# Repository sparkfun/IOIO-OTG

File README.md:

IOIO-OTG
========

[*IOIO-OTG (DEV-11343)*](https://www.sparkfun.com/products/11343)

The IOIO-OTG is a development board specifically designed for advanced hardware I/O capapbilities to your Android or PC application.
This board also allows the user to leverage USB On-The-Go specification to connect as a host or as an accessory. 

Repository Contents
-------------------
* **/Hardware** - All Eagle design files (.brd, .sch, .STL)
* **/Production** - Test bed files and production panel files

Documentation
--------------

* **[Hookup Guide](https://learn.sparkfun.com/tutorials/ioio-otg-hookup-guide)** - Basic hookup guide for the IOIO-OTG.
* **[SparkFun Fritzing repo](https://github.com/sparkfun/Fritzing_Parts)** - Fritzing diagrams for SparkFun products.
* **[SparkFun 3D Model repo](https://github.com/sparkfun/3D_Models)** - 3D models of SparkFun products. 
* **[SparkFun Graphical Datasheets](https://github.com/sparkfun/Graphical_Datasheets)** -Graphical Datasheets for various SparkFun products.

Product Versions
----------------
* [v22b](https://www.sparkfun.com/products/13613)- Version 2.2b. Currently for sale.
* [v21] (https://www.sparkfun.com/products/retired/12633)- Version 2.1. Retired.

Version History
---------------
* [v2.2b](https://github.com/sparkfun/IOIO-OTG/tree/V_2.2b) - GitHub files v2.2b
* [v2.1](https://github.com/sparkfun/IOIO-OTG/tree/V_2.1) - GitHub files v2.1

License Information
-------------------
This product is _**open source**_! 

Please review the LICENSE.md file for license information. 

If you have any questions or concerns on licensing, please contact techsupport@sparkfun.com.

Distributed as-is; no warranty is given.

- Your friends at SparkFun.

The IOIO is a collaboration with Ytai Ben-Tsvi. You can find his repo [here](https://github.com/ytai/ioio/wiki).

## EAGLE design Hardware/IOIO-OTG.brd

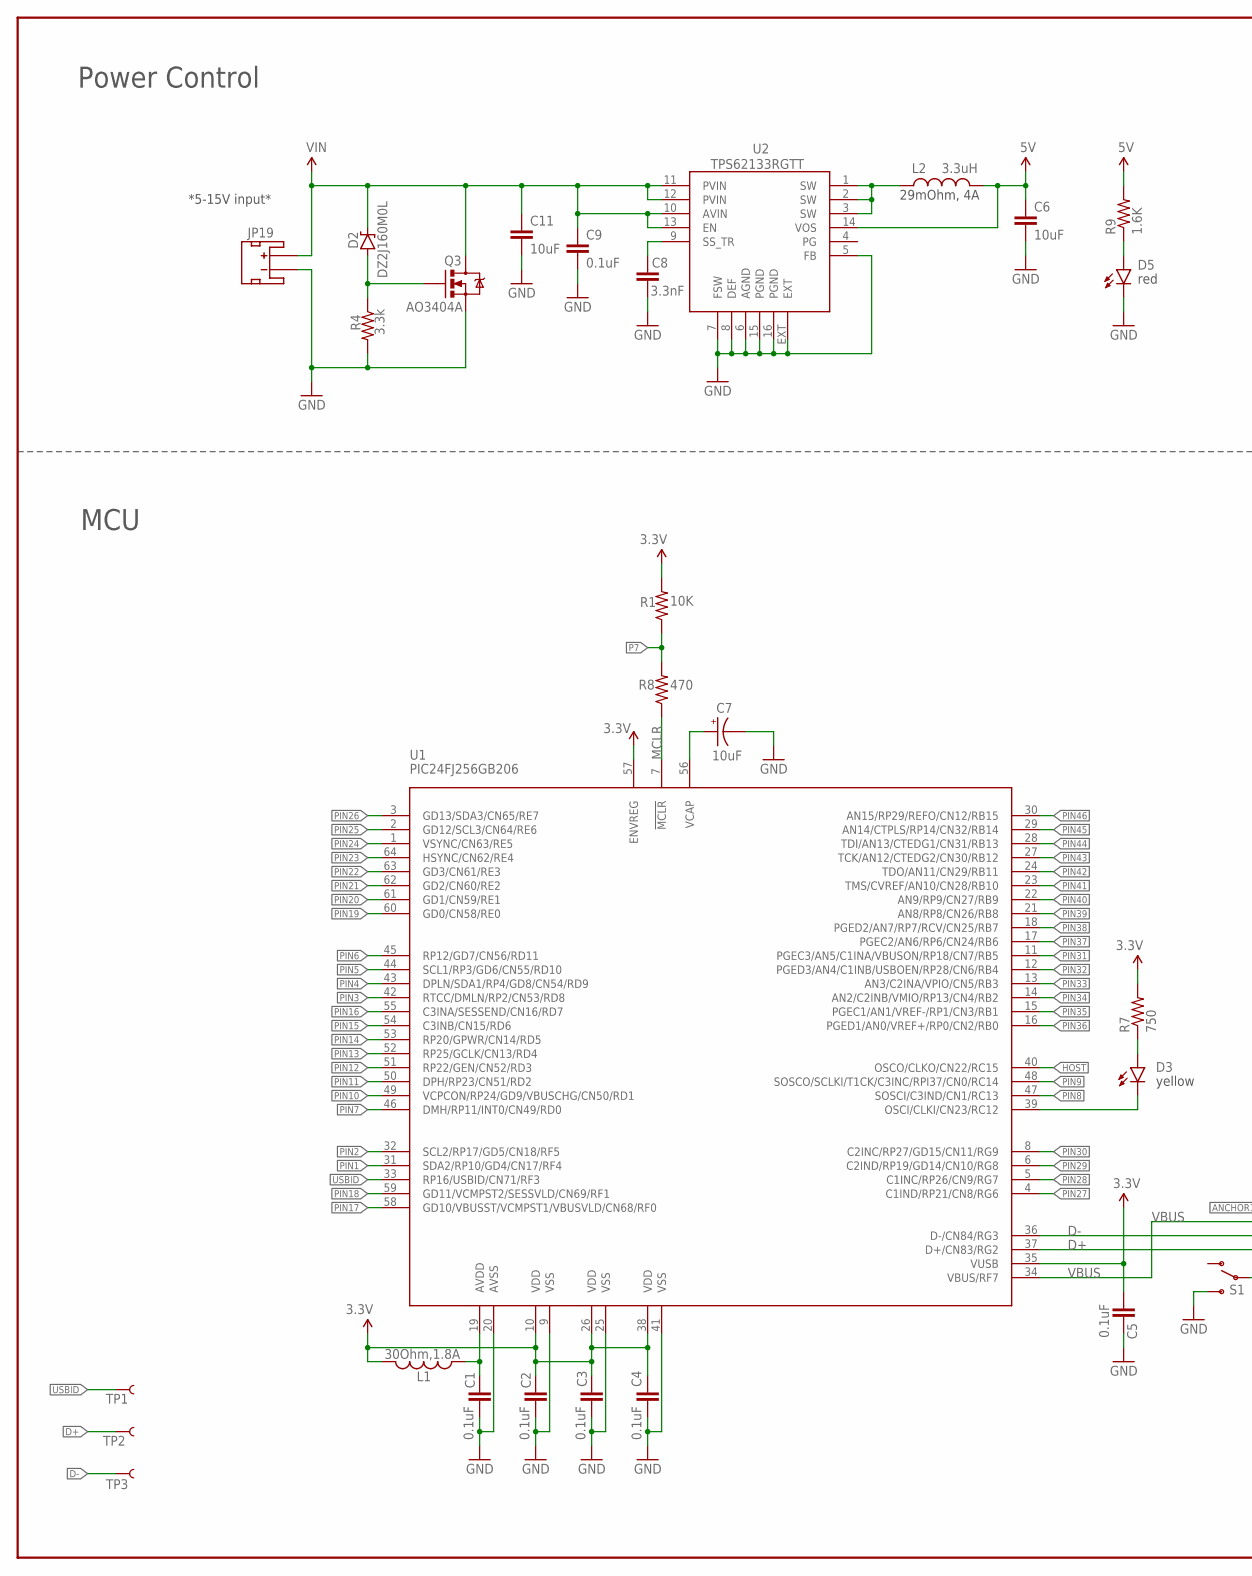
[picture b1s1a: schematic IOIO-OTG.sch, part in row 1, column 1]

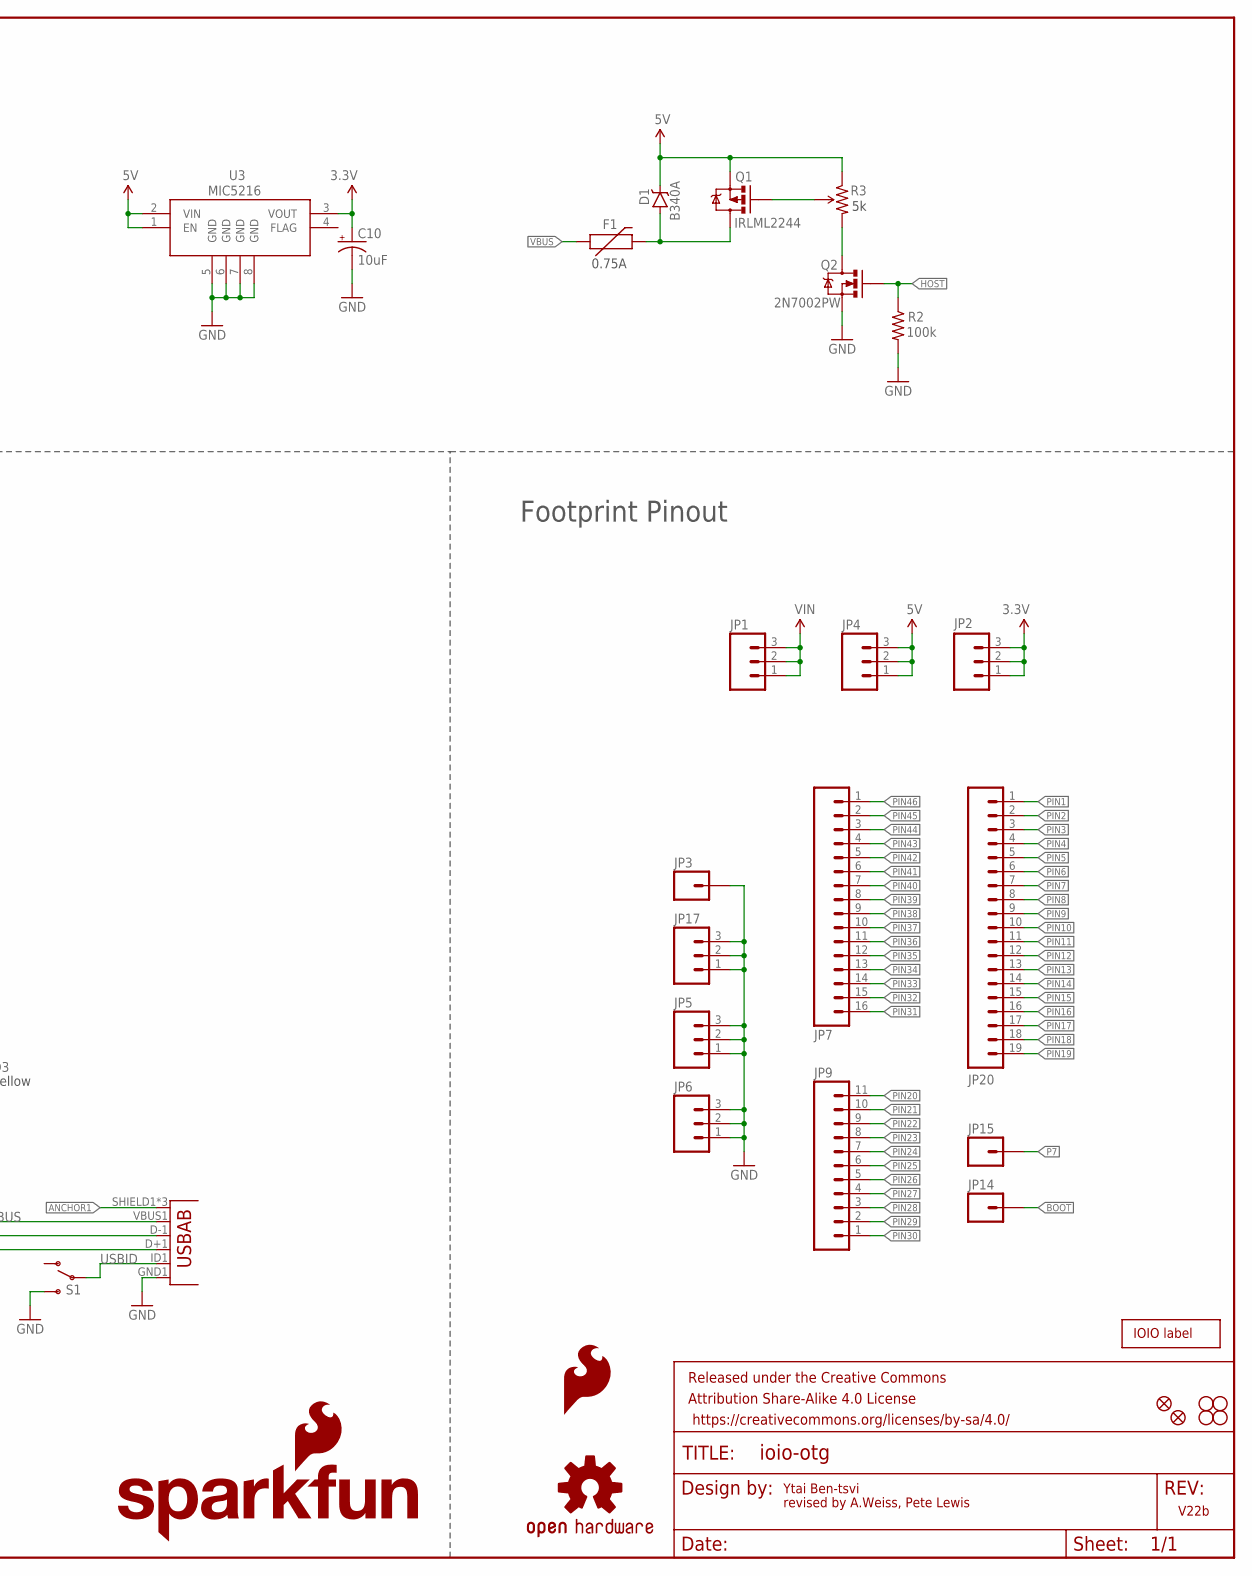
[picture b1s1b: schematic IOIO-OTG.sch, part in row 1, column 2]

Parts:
C1, C2, C3, C4, C5, C9: 0.1uF; 0603-CAP
C6: 10uF; 0805-CAP; PART# LMK212BJ106KG-T
C7: 10uF; EIA3216
C8: 3.3nF; 0603-CAP
C10: 10uF; EIA3216; PART# TAJA106K016RNJ
C11: 10uF; 1210; PART# UMK325C7106MM-T
D1: B340A; SMA-DIODE; PART# B340A
D2: DZ2J160M0L; PANASONIC_SMINI2-F5-B; PART# DZ2J150M0L
D3: Yellow; LED-0603
D5: Red; LED-0603
F1: 0.75A; PTC-1206; PART# 0ZCA0075FF2G
FRAME2: FRAME-LEDGER; CREATIVE_COMMONS
JP1, JP2, JP4, JP5, JP6, JP17: M03PTH; 1X03
JP3, JP14, JP15: M01PTH; 1X01
JP7: M161X16_NO_SILK; 1X16_NO_SILK
JP8, JP16: FIDUCIALUFIDUCIAL; MICRO-FIDUCIAL
JP9: M111X11_NO_SILK; 1X11_NO_SILK
JP10, JP11, JP12, JP13: STAND-OFF
JP19: JST; JST-2-SMD
JP20: M191X19_NO_SILK; 1X19_NO_SILK
JP21: AB MICRO USB; USB-AB-MICRO-SMD_V03
L1: 30Ohm,1.8A; 0603
L2: VLC5045T-3R3N; CR54
LOGO1: OSHW-LOGOS; OSHW-LOGO-S
LOGO2: SFE_LOGO_NAME_FLAME.1_INCH; SFE_LOGO_NAME_FLAME_.1
LOGO3: SFE_LOGO_FLAME.1_INCH; SFE_LOGO_FLAME_.1
Q1: IRLML2244; SOT23-3
Q2: 2N7002PW; SOT323; PART# 2N7002PW
Q3: MOSFET-NCHANNELAO3404A; SOT23-3; PART# AO3404A
R1: 10K; 0603-RES
R2: 100k; 0603-RES
R3: TS53YL502MR10; TRIMPOT_5MM; PART# TS53YL502MR10
R4: 3.3k; 0603-RES
R7: 750; 0603-RES
R8: 470; 0603-RES
R9: 1.6K; 0603-RES
S1: SWITCH_SPDT; KPS-1290
TP1, TP2, TP3: TEST-POINT3; PAD.03X.03
U1: PIC24FJ256GB206; PIC24FXXX_TQFP64
U2: TPS62133RGTT; QFN16-3X3MM_1:1_V03
U3: MIC5216; MSOP8
U$6: IOIO-OTG; IOIO-OTG-COPPER-EXPOSED

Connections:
3.3V: C2.1, C3.1, C4.1, C5.1, C10.A (+), JP2.1, JP2.2, JP2.3, L1.2, R1.2, R7.2, U1.10 (VDD), U1.26 (VDD), U1.35 (VUSB), U1.38 (VDD), U1.57 (ENVREG), U3.3 (VOUT)
5V: C6.1, D1.C, JP4.1, JP4.2, JP4.3, L2.P$2 (2), Q1.2 (S), R3.A (CCW), R9.2, U2.14 (VOS), U3.1 (EN), U3.2 (VIN)
ANCHOR1: JP21.SHIELD1 (SHIELD), JP21.SHIELD2 (SHIELD), JP21.SHIELD3 (SHIELD)
BOOT: D3.C, JP14.1, U1.39 (OSCI/CLKI/CN23/RC12)
D+: JP21.D+1 (D+), TP2.P$1, U1.37 (D+/CN83/RG2)
D-: JP21.D-1 (D-), TP3.P$1, U1.36 (D-/CN84/RG3)
GND: C1.2, C2.2, C3.2, C4.2, C5.2, C6.2, C7.C (-), C8.2, C9.2, C10.C (-), C11.2, D5.C, JP3.1, JP5.1, JP5.2, JP5.3, JP6.1, JP6.2, JP6.3, JP17.1, JP17.2, JP17.3, JP19.1 (-), JP21.GND1 (GND), Q2.2 (S), Q3.2 (S), R2.2, R4.2, S1.S, U1.9 (VSS), U1.20 (AVSS), U1.25 (VSS), U1.41 (VSS), U2.5 (FB), U2.6 (AGND), U2.7 (FSW), U2.8 (DEF), U2.15 (PGND), U2.16 (PGND), U2.EXT, U3.5 (GND), U3.6 (GND), U3.7 (GND), U3.8 (GND)
HOST: Q2.1 (G), R2.1, U1.40 (OSCO/CLKO/CN22/RC15)
MCLR: R8.1, U1.7 (!MCLR)
unnamed: Q1.1 (G), R3.B (WIPER)
unnamed: D3.A, R7.1
unnamed: D5.A, R9.1
unnamed: D1.A, F1.2, Q1.3 (D)
unnamed: C7.A (+), U1.56 (VCAP)
unnamed: L2.P$1 (1), U2.1 (SW), U2.2 (SW), U2.3 (SW)
unnamed: C8.1, U2.9 (SS_TR)
unnamed: Q2.3 (D), R3.C (CW)
unnamed: C1.1, L1.1, U1.19 (AVDD)
unnamed: D2.A, Q3.1 (G), R4.1
P7: JP15.1, R1.1, R8.2
PIN1: JP20.1, U1.31 (SDA2/RP10/GD4/CN17/RF4)
PIN2: JP20.2, U1.32 (SCL2/RP17/GD5/CN18/RF5)
PIN3: JP20.3, U1.42 (RTCC/DMLN/RP2/CN53/RD8)
PIN4: JP20.4, U1.43 (DPLN/SDA1/RP4/GD8/CN54/RD9)
PIN5: JP20.5, U1.44 (SCL1/RP3/GD6/CN55/RD10)
PIN6: JP20.6, U1.45 (RP12/GD7/CN56/RD11)
PIN7: JP20.7, U1.46 (DMH/RP11/INT0/CN49/RD0)
PIN8: JP20.8, U1.47 (SOSCI/C3IND/CN1/RC13)
PIN9: JP20.9, U1.48 (SOSCO/SCLKI/T1CK/C3INC/RPI37/CN0/RC14)
PIN10: JP20.10, U1.49 (VCPCON/RP24/GD9/VBUSCHG/CN50/RD1)
PIN11: JP20.11, U1.50 (DPH/RP23/CN51/RD2)
PIN12: JP20.12, U1.51 (RP22/GEN/CN52/RD3)
PIN13: JP20.13, U1.52 (RP25/GCLK/CN13/RD4)
PIN14: JP20.14, U1.53 (RP20/GPWR/CN14/RD5)
PIN15: JP20.15, U1.54 (C3INB/CN15/RD6)
PIN16: JP20.16, U1.55 (C3INA/SESSEND/CN16/RD7)
PIN17: JP20.17, U1.58 (GD10/VBUSST/VCMPST1/VBUSVLD/CN68/RF0)
PIN18: JP20.18, U1.59 (GD11/VCMPST2/SESSVLD/CN69/RF1)
PIN19: JP20.19, U1.60 (GD0/CN58/RE0)
PIN20: JP9.11, U1.61 (GD1/CN59/RE1)
PIN21: JP9.10, U1.62 (GD2/CN60/RE2)
PIN22: JP9.9, U1.63 (GD3/CN61/RE3)
PIN23: JP9.8, U1.64 (HSYNC/CN62/RE4)
PIN24: JP9.7, U1.1 (VSYNC/CN63/RE5)
PIN25: JP9.6, U1.2 (GD12/SCL3/CN64/RE6)
PIN26: JP9.5, U1.3 (GD13/SDA3/CN65/RE7)
PIN27: JP9.4, U1.4 (C1IND/RP21/CN8/RG6)
PIN28: JP9.3, U1.5 (C1INC/RP26/CN9/RG7)
PIN29: JP9.2, U1.6 (C2IND/RP19/GD14/CN10/RG8)
PIN30: JP9.1, U1.8 (C2INC/RP27/GD15/CN11/RG9)
PIN31: JP7.16, U1.11 (PGEC3/AN5/C1INA/VBUSON/RP18/CN7/RB5)
PIN32: JP7.15, U1.12 (PGED3/AN4/C1INB/USBOEN/RP28/CN6/RB4)
PIN33: JP7.14, U1.13 (AN3/C2INA/VPIO/CN5/RB3)
PIN34: JP7.13, U1.14 (AN2/C2INB/VMIO/RP13/CN4/RB2)
PIN35: JP7.12, U1.15 (PGEC1/AN1/VREF-/RP1/CN3/RB1)
PIN36: JP7.11, U1.16 (PGED1/AN0/VREF+/RP0/CN2/RB0)
PIN37: JP7.10, U1.17 (PGEC2/AN6/RP6/CN24/RB6)
PIN38: JP7.9, U1.18 (PGED2/AN7/RP7/RCV/CN25/RB7)
PIN39: JP7.8, U1.21 (AN8/RP8/CN26/RB8)
PIN40: JP7.7, U1.22 (AN9/RP9/CN27/RB9)
PIN41: JP7.6, U1.23 (TMS/CVREF/AN10/CN28/RB10)
PIN42: JP7.5, U1.24 (TDO/AN11/CN29/RB11)
PIN43: JP7.4, U1.27 (TCK/AN12/CTEDG2/CN30/RB12)
PIN44: JP7.3, U1.28 (TDI/AN13/CTEDG1/CN31/RB13)
PIN45: JP7.2, U1.29 (AN14/CTPLS/RP14/CN32/RB14)
PIN46: JP7.1, U1.30 (AN15/RP29/REFO/CN12/RB15)
USBID: JP21.ID1 (USBID), S1.P, TP1.P$1, U1.33 (RP16/USBID/CN71/RF3)
VBUS: F1.1, JP21.VBUS1 (VBUS), U1.34 (VBUS/RF7)
VIN: C9.1, C11.1, D2.C, JP1.1, JP1.2, JP1.3, JP19.2 (+), Q3.3 (D), U2.10 (AVIN), U2.11 (PVIN), U2.12 (PVIN), U2.13 (EN)

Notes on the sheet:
Ytai Ben-tsvi
revised by A.Weiss, Pete Lewis
*5-15V input*
yellow
red
0.75A
29mOhm, 4A
Footprint Pinout
Power Control
MCU
V22b
DZ2J160M0L
AO3404A
2N7002PW
IRLML2244
B340A

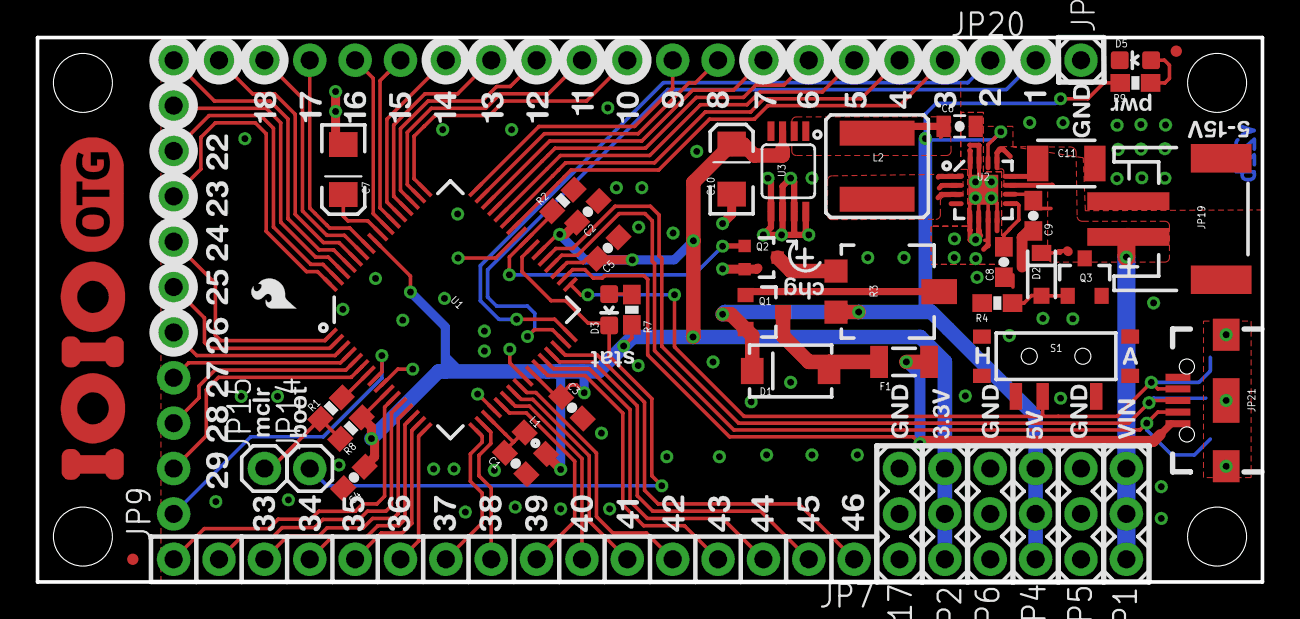
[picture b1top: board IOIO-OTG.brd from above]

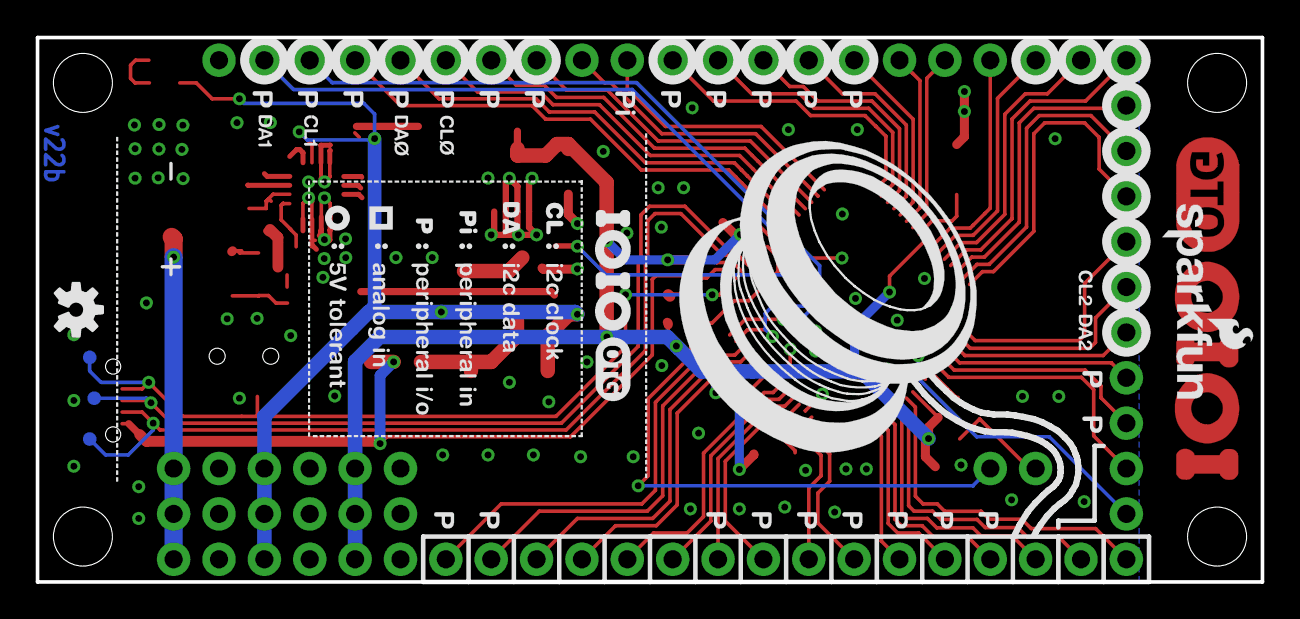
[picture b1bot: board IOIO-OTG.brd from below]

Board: 2 copper layers, 68.6 x 30.5 mm, 60 parts (5 on the bottom side), 69 nets.

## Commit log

2010-10-31 create repository
2010-12-16 Hardware V11
2011-01-20 first version of V12 from sparkfun
2011-01-21 board labeling fixes
2011-01-21 fixed mirrored bottom silk
2011-01-21 changed bottom silk design
2011-03-08 fixes to silk screen.
2011-03-08 added switching vreg. moved reset pin to .1" grid
2011-03-11 new hardware version. added switching vreg. grid-aligned reset pin. current limiting trimmer.
2011-04-07 hardware v1.4
2011-04-07 hardware v1.5
2011-10-19 Added make-all script
2011-10-20 Revised latency tester to support any connection type.
2011-10-21 moved make-all to tools
2012-02-19 Fix CRLF
2012-02-29 fix files damaged by crlf mess
2012-11-15 add all rxtx libraries as-is for easier tracking.
2012-11-19 why is it checked in???
2013-01-18 Added IOIO-OTG EAGLE files.
2013-08-01 Initial commit - gitignore, .brd and .sch
    pulled from KENTRO (v20)
2013-08-12 Heavy Revision
    (1) Created and added a new 1:1 FP for the TPS... IC
    (2) Routed all traces directly out from the TPS... IC
    (3) 0402 --> 0603
    (4) Created and added a new FP for a new microAB USB connector, this new
    FP is based off of the data-sheet for the new USB microAB that should
    have guiding bosses (very much trial right now).
2013-08-14 More changes:
    -removed test-points from below the microAB
    -Moved "PWR" LED and RES out just a bit more to clear headers on the OTG
    w/ Headers
    -Created and added a new TRIMPOT FP per Bob's request
    -Added T-Stop around the PIC to allow Tyler T. to be able to inspect the
    PIC with the AOI
2013-08-19 changed trimpot silk
2013-08-19 Added VBUS test-point and Tstop around VREG
2013-08-19 fixed inconsistency between BRD and SCH
2013-08-22 Consistency fixes
2013-08-22 Final 6.5.0 inconsistency fixes
2013-09-11 Added test-points
    3 new test-points:
    D+
    D-
    USBID
2013-09-11 Slight test-point position change
2013-09-11 Added vias below TPS IC for better GND flow
2013-09-11 Changed positions of Test-Points
2013-10-10 Created Panels
2014-02-06 Updating README
2014-12-03 hardware: Fixed brd file to make annotation happy
2015-04-09 BRD/SCH from 3/11, includes new power protection
2015-04-09 Switch USB connector to part with mounting bosses
    Also included an anchor polygon to strengthen mounting pads.
2015-04-09 Moved OSHW logo to proper device
    Also moved measures to measure layer and changed units to inches
2015-04-09 Moved R1, R8, C4 to proper 0603 packages
    All three components had to move slightly. This will require updating
    their x/y coordinates.
2015-04-09 Moved C1 and L1 to proper 0603 packages
    moved X/Y coordinates
2015-04-09 Moved C3 to proper 0603 package
    moved X/Y coordinate
2015-04-10 All remaining 0402 passives bumped to 0603
    all components had slight shift in X/Y coordinates. Components near the
    TPS6124 also requires some shifting. Included an "original" and "moved
    to 0603" screen shot of design for review.
2015-04-10 removed backup files added gitignore
2015-04-10 Moved to v22 in sch/copper, updated frame in SCH
2015-04-10 Restored back to 1.6K and 750 ohm LED resistors
2015-04-20 Clearance errors
    Set DRC to 7 mil (our standard is 8, but this design is really tight).
    very slight shifting of some traces to fix clearance errors.
2015-04-20 updated pic24 IC device, add tstop between legs
    The white solder mask in between the legs on the IC was causing the AOI
    to throw tons of false calls. removing the mask solves the issue.
2015-04-20 moved to SFE logo
    both mini flame on top, and backside name/flame
2015-04-20 DFM routing for TPS chip
    -added tRestrict to separate pads on TPS chip.
    -changed copper to v22b
2015-04-20 v22b in copper and sch
2015-04-22 Schematic Cleanup
    flags, spacing, revisor
2015-04-23 swapping out devices to include PROD_IDs
2015-04-23 more PROD_IDs
2015-04-24 Package update on D2 (zener) and PROD_IDs
    Had to scoot upwards on most of the power circuit components to make
    space for the correct package size on the zener.
    All PROD_IDs done.
2015-04-24 Schematic Cleanup
2015-04-27 updated to vector outlines on ioio copper logo
2015-04-27 approving drc width erros on copper logo
2015-04-27 changing some of the silk over to vectors
    -dashed lines on bplace
    -charge current arrow and "+"
2015-04-27 Bottom silk logo to vector
    also moved bstop star to vector
2015-04-27 Staking vias under USB connector
    Note, had to move test point 3
2015-04-27 ensuring all parts have name/value in board file
    Also arranged them nicely for assembly sheet
2015-04-27 cleaned up measures
2015-04-27 updated polarity and outline silk on some parts
    pic24, tps, trimpot, switch
2015-04-27 nudged 'stat' led silk to avoid via
2015-04-29 4-way junctions in sch
2015-04-30 Seed logo
2015-04-30 SparkFun Logo
2015-11-25 Adding in hardware changes from Pete
2015-11-25 Re-adding changes
2015-11-25 removing duplicate files
2015-11-30 Value text object to sch for D1, D2, Q1, Q2, Q3
    I used part #s for values (rather than the "values") for these
    components. This is to ensure production (and users) will know when they
    are a different component, when looking at the schematic. Note they are
    text objects living in the wild, and not actually part of the device in
    the library. Although, the values are inside the properties for each
    device as well.
2015-11-30 switched to "TIGHT" DRU, bumped vias up to 15 mil
    Note, when I moved to the TIGHT DRU the restring for vias is set to 7
    mil (this makes for a tighter annular ring). The previous DRU settings
    had the restring set at 10 mil, and all of the vias were 12 mil drills.
    When I changed to a 7 mil restring and a 15 mil drill, the vias were
    still a smaller footprint than in the original. So ultimately, this
    didn't necessitate any component moving or trace re-routing.
2015-12-04 created panel v22b
2016-06-02 Removing old files, adding license and .git files, updating README with product and tutorial links

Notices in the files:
parts and their libraries:
SparkFun-PowerIC: Licensing: CC v3.0 Share-Alike You are welcome to use this library for commercial purposes.
SparkFun-Aesthetics: Released under the Creative Commons Attribution Share-Alike 4.0 License
SparkFun-Aesthetics: https://creativecommons.org/licenses/by-sa/4.0
